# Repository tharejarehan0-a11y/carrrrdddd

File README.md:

# BlE badges
The best badges for you and your friends. Find your friends whenever and whereever you want to find them if they are near you 

# Version 1 Idea
The idea for version 1 was that first let's only create some badges that js light up when your friends show up sometime near you and you are trying to find them so the badges light up the more when you more near to themn 

# Schematics 

The schematics were easy tho but the hard part was js to make the battery contrast with all other components as lipo is bigger but coin cells js dont do it so we decided to be on lipo for now 
# 3D view

# PCB

This is the pcb and it is black in color when i ordered it as it contrasted well with the white color of the silkscreen
# Problems Faces
I started with an IC and then i came to the decision that because of the time shortatge i might need to switch to modules and then i switched to modules and started using them

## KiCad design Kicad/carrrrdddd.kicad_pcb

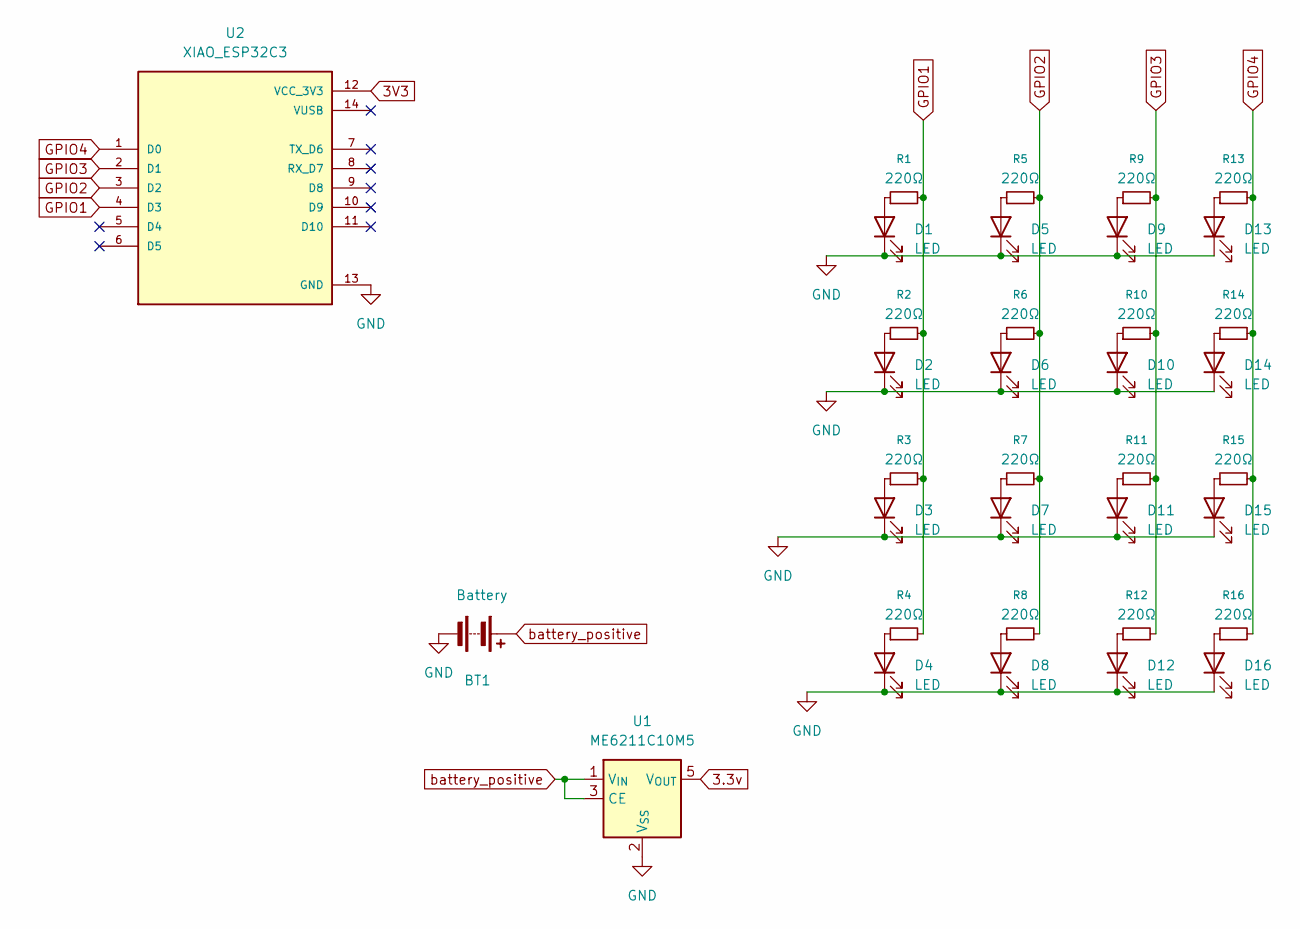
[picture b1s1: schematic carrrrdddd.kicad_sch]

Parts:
BT1: Battery; JST_PH_B2B-PH-K_1x02_P2.00mm_Vertical
D1, D2, D3, D4, D5, D6, D7, D8, D9, D10, D11, D12, D13, D14, D15, D16: LED; LED_0603_1608Metric
R1, R2, R3, R4, R5, R6, R7, R8, R9, R10, R11, R12, R13, R14, R15, R16: 220Ω; R_0603_1608Metric
U1: ME6211C10M5; SOT-23-5
U2: XIAO_ESP32C3; MODULE_XIAO_ESP32C3; PARTREV 23/05/2022

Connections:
GND: BT1.2 (-), D1.1 (K), D2.1 (K), D3.1 (K), D4.1 (K), D5.1 (K), D6.1 (K), D7.1 (K), D8.1 (K), D9.1 (K), D10.1 (K), D11.1 (K), D12.1 (K), D13.1 (K), D14.1 (K), D15.1 (K), D16.1 (K), U1.2 (V_{SS}), U2.13 (GND)
GPIO1: R1.2, R2.2, R3.2, R4.2, U2.4 (D3)
GPIO2: R5.2, R6.2, R7.2, R8.2, U2.3 (D2)
GPIO3: R9.2, R10.2, R11.2, R12.2, U2.2 (D1)
GPIO4: R13.2, R14.2, R15.2, R16.2, U2.1 (D0)
unnamed: D1.2 (A), R1.1
unnamed: D2.2 (A), R2.1
unnamed: D3.2 (A), R3.1
unnamed: D4.2 (A), R4.1
unnamed: D5.2 (A), R5.1
unnamed: D6.2 (A), R6.1
unnamed: D7.2 (A), R7.1
unnamed: D8.2 (A), R8.1
unnamed: D9.2 (A), R9.1
unnamed: D10.2 (A), R10.1
unnamed: D11.2 (A), R11.1
unnamed: D12.2 (A), R12.1
unnamed: D13.2 (A), R13.1
unnamed: D14.2 (A), R14.1
unnamed: D15.2 (A), R15.1
unnamed: D16.2 (A), R16.1
battery_positive: BT1.1 (+), U1.1 (V_{IN}), U1.3 (CE)

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
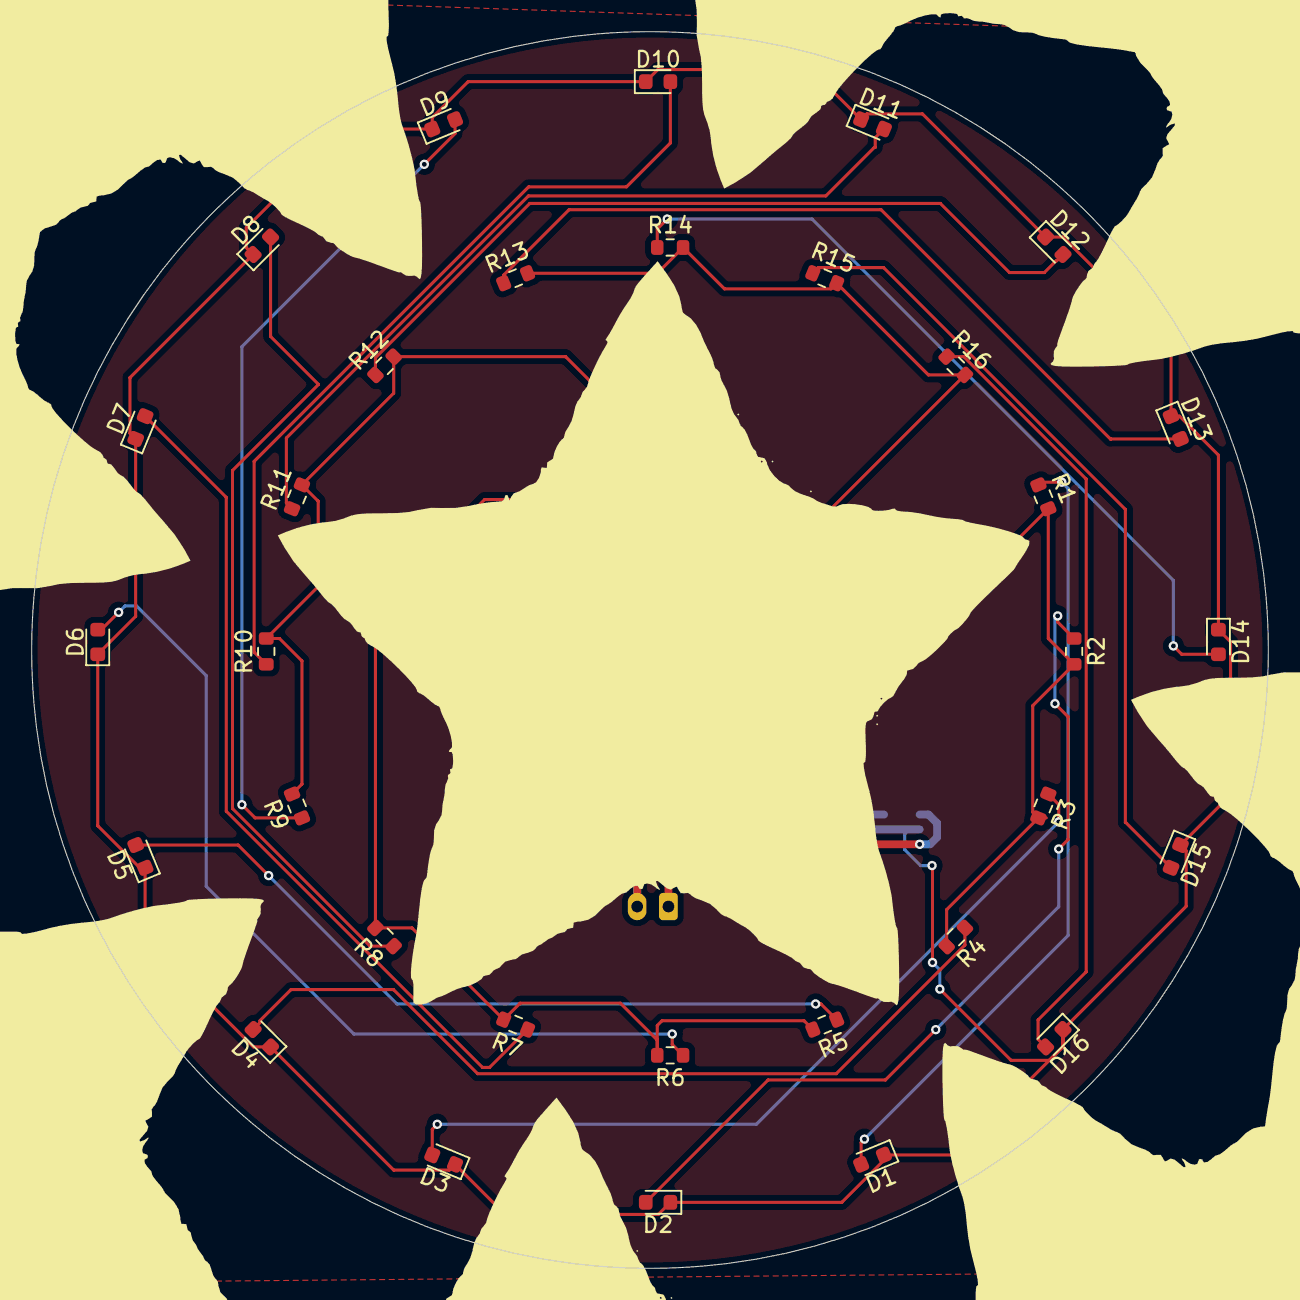
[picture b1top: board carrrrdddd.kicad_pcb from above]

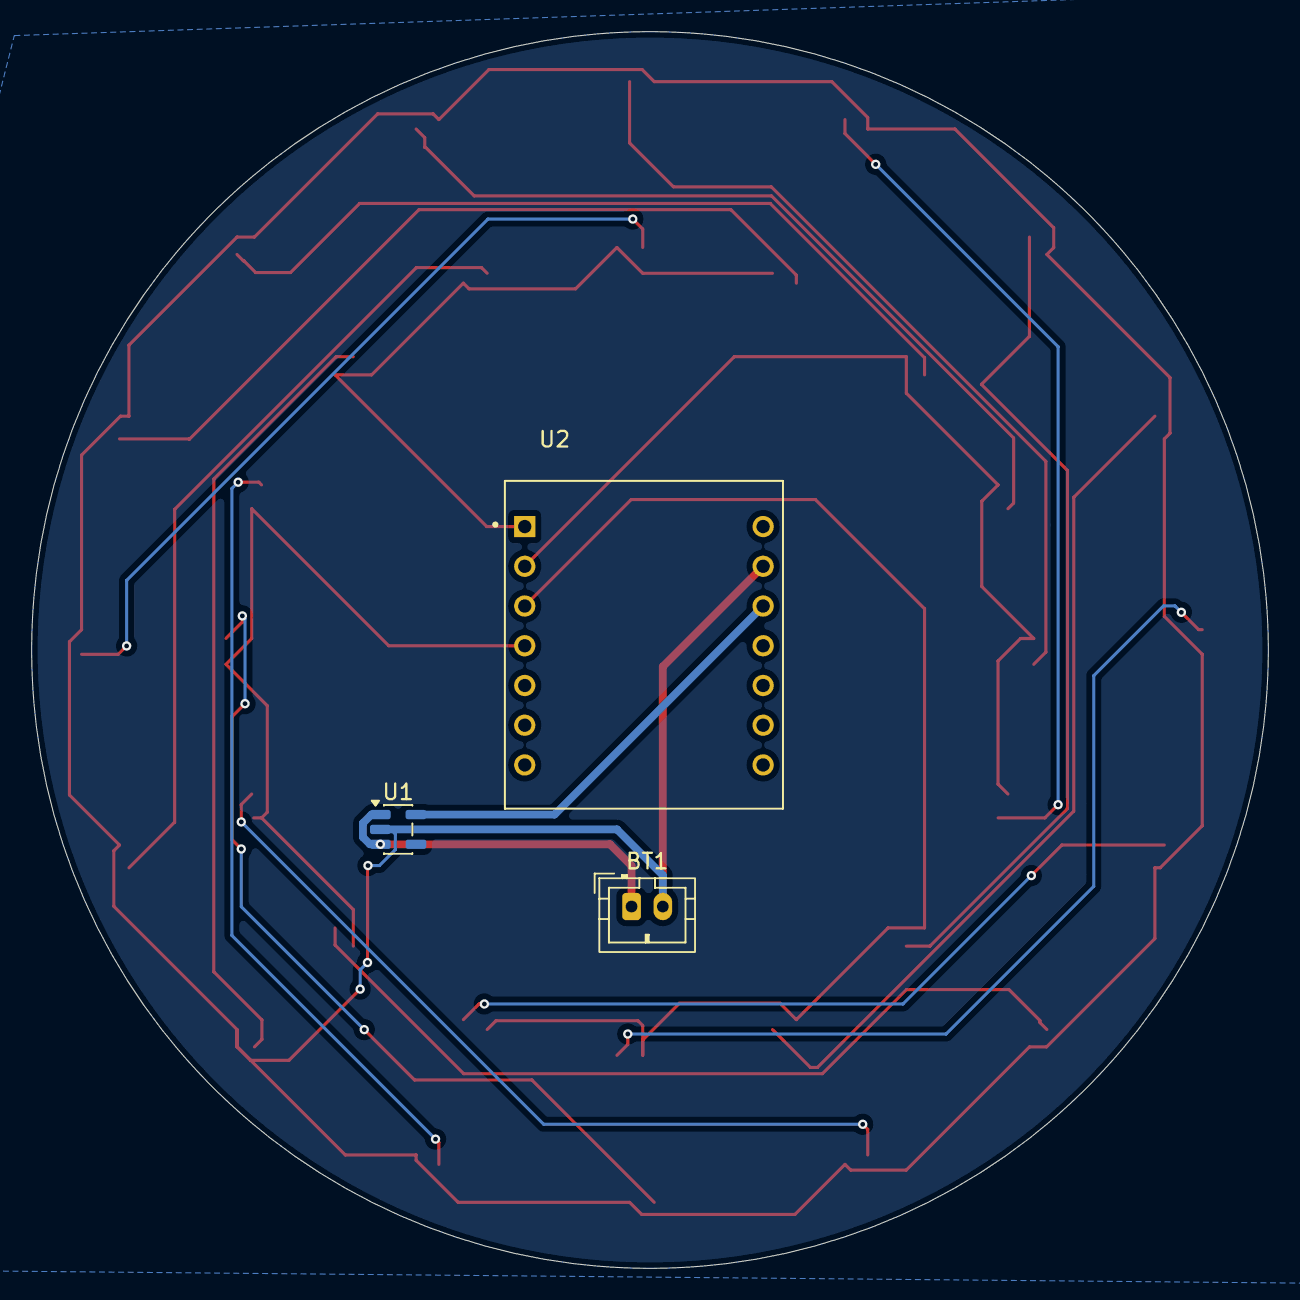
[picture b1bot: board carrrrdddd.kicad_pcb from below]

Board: 2 copper layers, 79.1 x 79.1 mm, 35 parts (3 on the bottom side), 23 nets.

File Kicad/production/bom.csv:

Designator,Footprint,Quantity,Value,LCSC Part #
BT1,JST_PH_B2B-PH-K_1x02_P2.00mm_Vertical,1,Battery,
"D1, D10, D11, D12, D13, D14, D15, D16, D2, D3, D4, D5, D6, D7, D8, D9",0603,16,LED,
"R1, R10, R11, R12, R13, R14, R15, R16, R2, R3, R4, R5, R6, R7, R8, R9",0603,16,220Ω,
U1,SOT-23-5,1,ME6211C10M5,
U2,MODULE_XIAO_ESP32C3,1,XIAO_ESP32C3,
